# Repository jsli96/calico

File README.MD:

# Calico 🤖

**Calico** is a miniature relocatable wearable system with fast and precise locomotion for on-body interaction, actuation and sensing. 
Calico consists of a two-wheel robot and an on-cloth track mechanism or "railway," on which the robot travels. 
The robot is self-contained, small in size, and has additional sensor expansion options. 
The Calico robot can adapt for various applications and target for different audience such as older adults, dancers, and children. 
For example, we designed **[Dance^2](https://dancesquared.xyz/)** with Calico to explore new forms of dance and movement, and to create a new form of interaction.
We also investigate how **[Calico for older adults](https://dl.acm.org/doi/10.5555/3721488.3721562)** can assist with daily activities and provide companionship. 

Please see the [Calico website](https://smartlab.cs.umd.edu/publication/calico) and [papers](https://dl.acm.org/doi/10.1145/3715336.3735828) for more details on the design and applications of Calico, and if you use Calico in your work, please consider to cite the following papers:
```
@article{sathya2022calico,
  title={Calico: Relocatable On-cloth Wearables with Fast, Reliable, and Precise Locomotion},
  author={Sathya, Anup and Li, Jiasheng and Rahman, Tauhidur and Gao, Ge and Peng, Huaishu},
  journal={Proceedings of the ACM on Interactive, Mobile, Wearable and Ubiquitous Technologies},
  volume={6},
  number={3},
  pages={1--32},
  year={2022},
  publisher={ACM New York, NY, USA}
}
```

```
@inproceedings{sathya2025cybernetic,
  title={Cybernetic Marionette: Channeling Collective Agency Through a Wearable Robot in a Live Dancer-Robot Duet},
  author={Sathya, Anup and Li, Jiasheng and Yan, Zeyu and Fang, Adriane and Kules, Bill and Martin, Jonathan David and Peng, Huaishu},
  booktitle={Proceedings of the 2025 ACM Designing Interactive Systems Conference},
  pages={3326--3340},
  year={2025}
}
```
```
@inproceedings{antony2025design,
  title={The design of on-body robots for older adults},
  author={Antony, Victor Nikhil and Jeon, Clara and Li, Jiasheng and Gao, Ge and Peng, Huaishu and Ostrowski, Anastasia K and Huang, Chien-Ming},
  booktitle={2025 20th ACM/IEEE International Conference on Human-Robot Interaction (HRI)},
  pages={589--598},
  year={2025},
  organization={IEEE}
}
```

---

## 📦 Table of Contents

- [Features](#-features)  
- [Hardware setup (BOM)](#-hardware)  
- [Arduino configuration](#arduino-configuration)
- [Connect & control the robot](#connect--control-the-robot)
- [Tips](#tips)

---

## ✨ Features

- MCU: ESP32 S3-Zero (Powered by [Waveshare](https://www.waveshare.com/wiki/ESP32-S3-Zero)) 
- Graphical user interface (GUI) for real time control
- Wi-Fi connection and controlled
- LED strip for visual feedback
- DC Motor Driver: DRV 8835
- LiPo's battery powered and charge via USB-C

---

## 🔧 Hardware

### Robot body and tracks 

- [Main body](./3D%20print%20models) 
  - 3D print material: PLA or Carbon PLA
  - Recommended print settings: 
    - Layer height: 0.2mm
    - Infill: 20% (or more for stronger body)
    - Print angle: 30 degrees
    - Supports: Yes 
  - Bamboo project file is included for reference: [3MF file](./3D%20print%20models/main_body.3mf)

- [Body cap](./3D%20print%20models) (Recommended setting same as above)
  - Require M2 screws and insert nuts to attach the body cap to the main body.
- [Wheels](./3D%20print%20models) (3D print material: PLA or Carbon PLA)
- [Track](./3D%20print%20models)
  - 3D print material: TPU Shore-95A
  - Recommended print settings: 
    - Layer height: 0.2mm
    - Infill: 20% 
    - Print angle: Flat (0 degrees)
    - Supports: Yes 
  - Bamboo project file is included for reference: [3MF file](./3D%20print%20models/track.3mf)
  - Tracks are designed in modular pieces, and you can print multiple pieces to create a longer track. 
    To connect the track pieces, you need a 1.75mm filament (e.g., PLA) and insert them into designed holes at the both end of the track pieces.
    
  - See below figures for references.

### Robot electronics

- MCU ([ESP32 S3-Zero](https://www.waveshare.com/wiki/ESP32-S3-Zero))
- Custom PCB ([See PCB folder for details](./PCB%20files))
- N20 DC motors
- LED strip (4 LEDs)
- 3.7V LiPo battery

---

## Arduino Configuration
The robot is powered by an ESP32 S3-Zero, which is programmed using the Arduino IDE. 
Please refer to the below steps to set up the Arduino IDE for Calico.
- Install the [Arduino IDE](https://www.arduino.cc/en/software).
- Open Arduino IDE settings (Mac Version) `Arduino IDE` (the top-left corner on the screen) > `Settings`, (Win version) `File` > `Preferences` 
- Adding the following URL to the "Additional Boards Manager URLs" field:
  ```
  https://dl.espressif.com/dl/package_esp32_index.json
  ```
- Open the Boards Manager from `Tools` > `Board` > `Boards Manager`, search for `esp32`. Then install the latest version of `esp32 by Espressif Systems`.
- Select the ESP32 S3-Zero board from `Tools` > `Board` > `ESP32 S3 Dev Module`.
- Refer to the below image to configure the ESP32 settings:
- 

---

## Connect & control the robot
To connect and control the robot, follow these steps:
1. **Connect the robot to your computer** using a USB-C cable.
2. **Open the Arduino IDE** and select the correct port from `Tools` > `Port`.
3. **Change the WiFi credentials** in the `main_app.ino' file (line 46 - 49) to match your network:
   ```
   const char* ssid_dev = "your-ssid";
   const char* password_dev = "your-password";
   const char* ssid = "your-ssid";
   const char* password = "your-password";
   ```
4. **Upload the code** to the ESP32 S3-Zero by clicking the upload button in the Arduino IDE. (You only need to do this once. 
After you have updated the Wi-Fi credentials and uploaded the code into Calico robot, you can control the robot without needing to upload the code again.)
   - Make sure you have the correct board and port selected in the Arduino IDE.
   - The upload process may take a few minutes, and you will see the progress in the console at the bottom of the IDE.
5. Once the upload is complete, open the Serial Monitor from `Tools` > `Serial Monitor` to see the connection status.
6. If the robot connects successfully, you will see a message indicating the IP address assigned to the robot.
7. **Open the GUI** by navigating to the IP address in your web browser. The GUI will allow you to control the robot's movement and LED strip.

## Tips
1. The robot will light up the LED light on board in different colors based on its status:
   - **light off**: Robot not powered
   - **steady blue**: Wi-Fi connected
   - **flashing blue**: Trying to connect Wi-Fi
   
2. If you can not see the ip address from the serial port you can use LanScan tools to find the IP address of the robot. 
   - For example, you can use [LanScan](https://apps.apple.com/us/app/lanscan/id472226235?mt=12) or [Advanced IP Scanner](https://www.advanced-ip-scanner.com/).

3. Battery connector is JST PH 2.0, and motor and LED connectors are JST SH 1.0.
4. The robot can be charged via USB-C port. (**be careful with the battery +/- directions**)
   - The battery is 3.7V LiPo battery, and the charging current is 500mA.
   - The battery can be replaced if needed.

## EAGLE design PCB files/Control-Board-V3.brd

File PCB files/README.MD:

This is the PCB files folder for the Calico project. It contains the schematic and PCB design files for the custom control board used in the Calico robot.

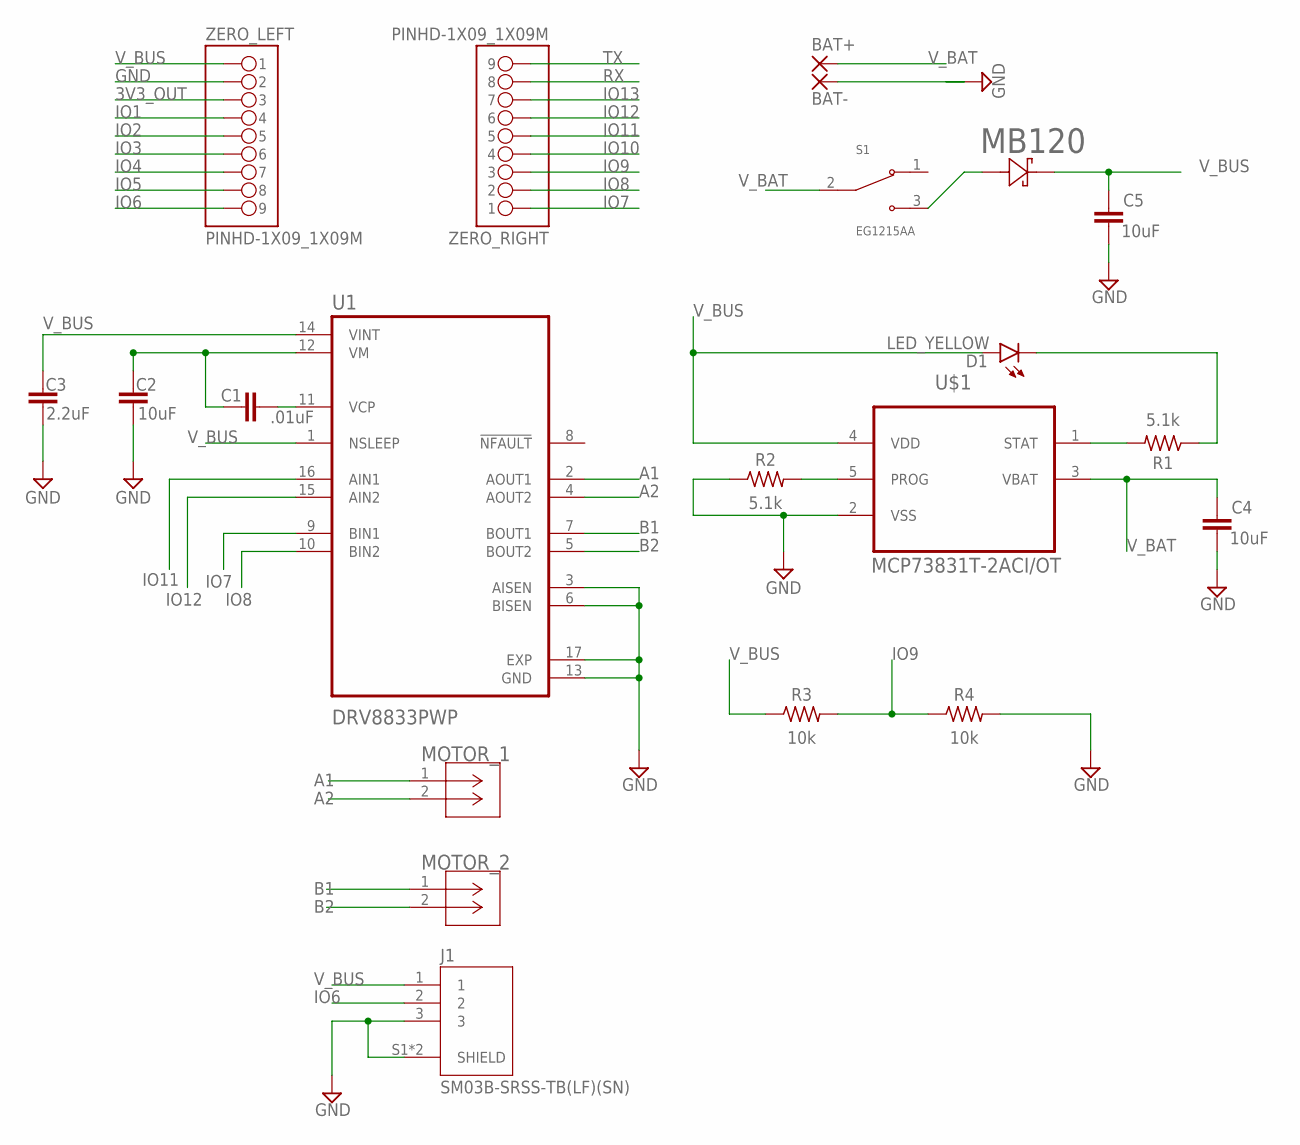
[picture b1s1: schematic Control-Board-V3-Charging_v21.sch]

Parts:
BAT+: SMD2; SMD1,27-2,54
BAT-: SMD2; SMD1,27-2,54
C1: .01uF; CAPC2012X110
C2, C4, C5: 10uF; CAPC2012X110
C3: 2.2uF; CAPC2012X110
D1: LED_YELLOW; LEDC2012X110N_FLAT-Y
J1: SM03B-SRSS-TB(LF)(SN); JST_SM03B-SRSS-TB(LF)(SN)
MB120: MBR120LSFT3GSDO_SOD-123FL(498)_OSI-L; SDO_SOD-123FL(498)_OSI-L
MOTOR_1, MOTOR_2: JST_SH; JST
R1, R2: 5.1k; RESC2012X65
R3, R4: 10k; RESC2012X65
S1: EG1215AA; SW_EG1215AA
U1: DRV8833PWP; IC_DRV8833PWP
U$1: MCP73831T-2ACI/OT; SOT95P280X145-5N
ZERO_LEFT: PINHD-1X09_1X09M; 1X09
ZERO_RIGHT: PINHD-1X09_1X09M; 1X09

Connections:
3V3_OUT: ZERO_LEFT.3
A1: MOTOR_1.1, U1.2 (AOUT1)
A2: MOTOR_1.2, U1.4 (AOUT2)
B1: MOTOR_2.1, U1.7 (BOUT1)
B2: MOTOR_2.2, U1.5 (BOUT2)
GND: BAT-.1, C2.1, C3.1, C4.2, C5.2, J1.3, J1.S1 (SHIELD), J1.S2 (SHIELD), R2.1, R4.2, U1.3 (AISEN), U1.6 (BISEN), U1.13 (GND), U1.17 (EXP), U$1.2 (VSS), ZERO_LEFT.2
IO1: ZERO_LEFT.4
IO2: ZERO_LEFT.5
IO3: ZERO_LEFT.6
IO4: ZERO_LEFT.7
IO5: ZERO_LEFT.8
IO6: J1.2, ZERO_LEFT.9
IO7: U1.9 (BIN1), ZERO_RIGHT.1
IO8: U1.10 (BIN2), ZERO_RIGHT.2
IO9: R3.2, R4.1, ZERO_RIGHT.3
IO10: ZERO_RIGHT.4
IO11: U1.16 (AIN1), ZERO_RIGHT.5
IO12: U1.15 (AIN2), ZERO_RIGHT.6
IO13: ZERO_RIGHT.7
unnamed: C1.2, U1.11 (VCP)
unnamed: R1.2, U$1.1 (STAT)
unnamed: D1.C, R1.1
unnamed: R2.2, U$1.5 (PROG)
unnamed: MB120.2, S1.3
RX: ZERO_RIGHT.8
TX: ZERO_RIGHT.9
V_BAT: BAT+.1, C4.1, S1.2, U$1.3 (VBAT)
V_BUS: C1.1, C2.2, C3.2, C5.1, D1.A, J1.1, MB120.1, R3.1, U1.1 (NSLEEP), U1.12 (VM), U1.14 (VINT), U$1.4 (VDD), ZERO_LEFT.1

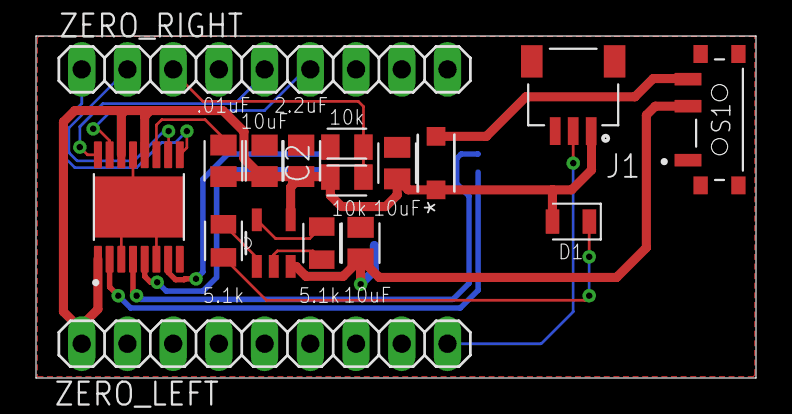
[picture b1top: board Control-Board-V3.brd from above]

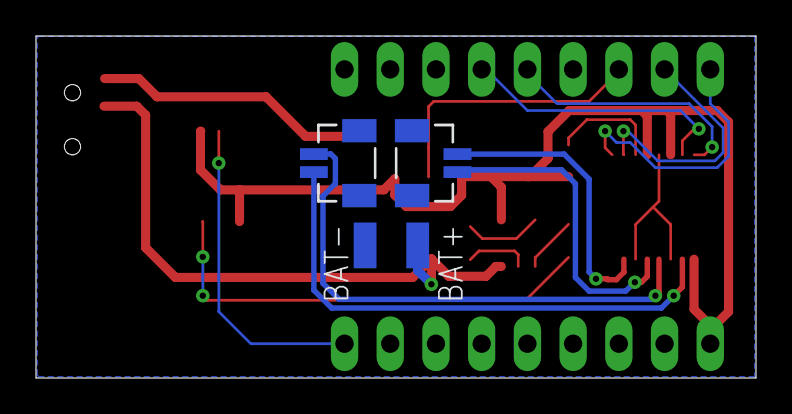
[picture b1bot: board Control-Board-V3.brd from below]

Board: 2 copper layers, 40.0 x 19.0 mm, 21 parts (4 on the bottom side), 18 nets.

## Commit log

2023-01-09 Update README.md
    update readme
2023-01-09 update new files
    web buttons updated
2023-01-18 Add simplified on bot code
2023-02-23 buzzy, and auto changing finished, fade not yet.
2023-02-24 Fading finished...
2023-03-04 reverse moving direction.
2023-03-04 added white led
2023-03-04 reordered the buttons
2023-03-04 decrease the led auto changing time interval.
2023-03-04 decrease the white led power to 55/255
2023-03-08 add fast led auto changing
2025-07-17 reorg folder, empty space for calico 2.0 files
2025-07-17 update calico 2.0 files

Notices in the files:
parts and their libraries:
MB120: COPYRIGHT: Copyright (C) 2024 Ultra Librarian. All rights reserved.
